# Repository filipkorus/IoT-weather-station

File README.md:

### Development
- [backend README](backend/README.md)
- [frontend README](frontend/README.md)

### Production
Build:
```shell
docker compose -f compose-master.yml -f compose-local.yml build
```

Start:
```shell
docker compose -f compose-master.yml -f compose-local.yml up -d
```

**NOTE:** [example-compose-local.yml](example-compose-local.yml) file is an example how [compose-local.yml](compose-local.yml) file should look like.

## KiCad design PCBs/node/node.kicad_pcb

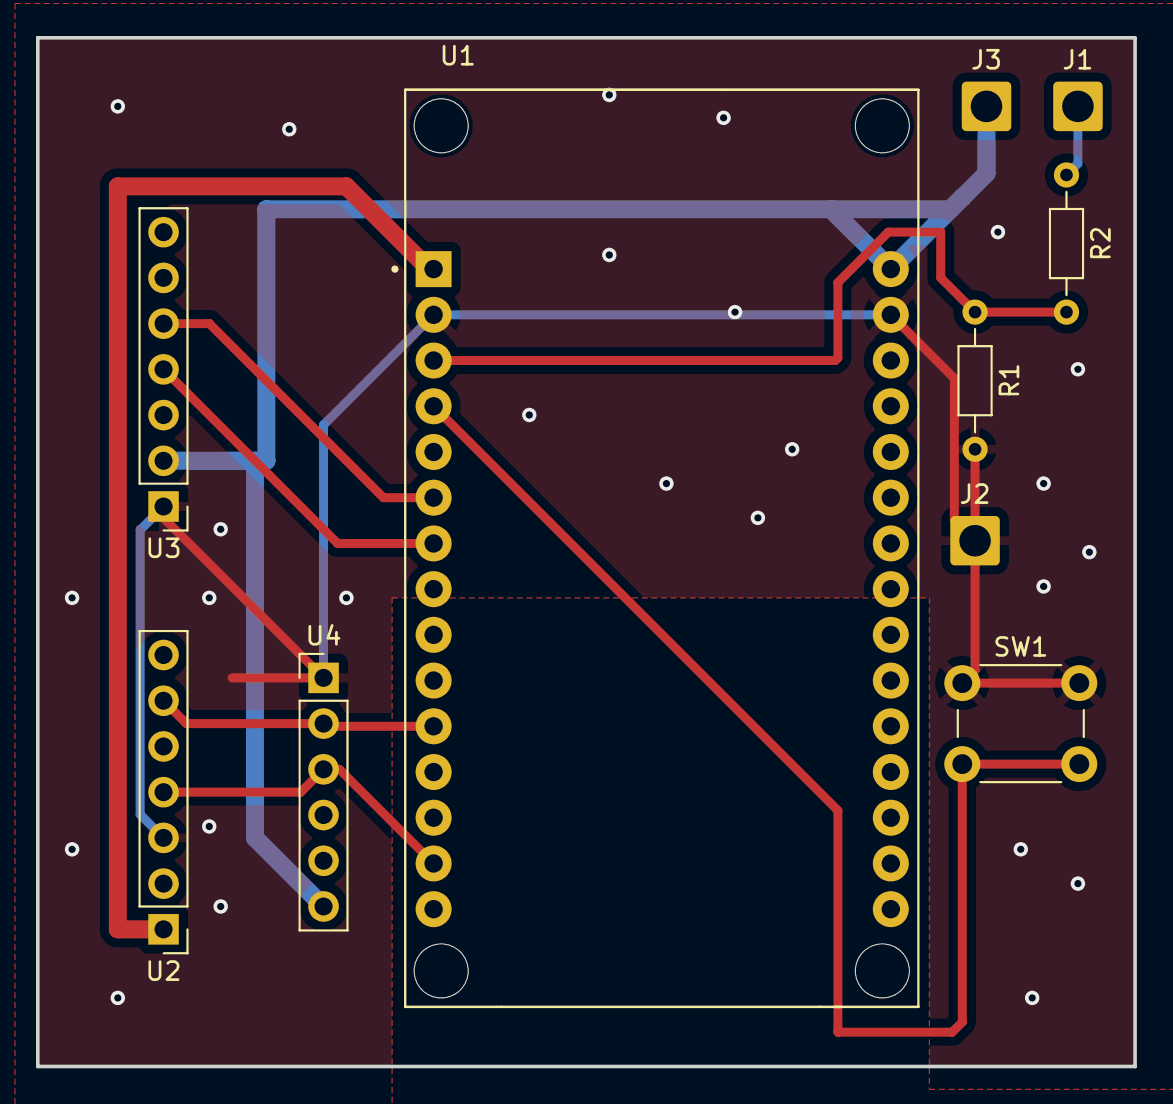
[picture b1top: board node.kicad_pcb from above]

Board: 2 copper layers, 61.0 x 57.2 mm, 10 parts (0 on the bottom side), 10 nets.

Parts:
J1: Bat+; SolderWire-1sqmm_1x01_D1.4mm_OD2.7mm
J2: GND; SolderWire-1sqmm_1x01_D1.4mm_OD2.7mm
J3: 5V; SolderWire-1sqmm_1x01_D1.4mm_OD2.7mm
R1: 10k; R_Axial_DIN0204_L3.6mm_D1.6mm_P7.62mm_Horizontal
R2: 20k; R_Axial_DIN0204_L3.6mm_D1.6mm_P7.62mm_Horizontal
SW1: SW_Push; SW_PUSH_6mm
U1: ESP32-DEVKIT-V1; MODULE_ESP32_DEVKIT_V1
U2: BME280; PinHeader_1x07_P2.54mm_Vertical
U3: pm25sensor; PinHeader_1x07_P2.54mm_Vertical
U4: lidar; PinHeader_1x06_P2.54mm_Vertical

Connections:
+3.3V: U1.1 (3V3), U2.1 (VIN)
+5V: J3.1, U1.30 (VIN), U3.2 (VCC), U4.6 (VCC)
GND: J2.1, R1.2, SW1.1, U1.2 (GND), U1.29 (GND), U2.3 (GND), U3.1 (GND), U4.1 (GND)
unnamed: J1.1, R2.1
unnamed: SW1.2, U1.4 (D2)
unnamed: R1.1, R2.2, U1.3 (D15)
unnamed: U1.11 (D21), U2.6 (SDI), U4.2 (SDA)
unnamed: U1.14 (D22), U2.4 (SCK), U4.3 (SCL)
unnamed: U1.6 (RX2), U3.5 (TX)
unnamed: U1.7 (TX2), U3.4 (RX)

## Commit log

2024-10-13 hotfix
2024-10-13 make WebSockets pass reverse proxy
2024-10-13 page title
2024-10-16 created PIO project with basic test program
2024-10-16 remove .vscode
2024-10-16 Created PIO project with basic test program (#1)
    * created PIO project with basic test program
    * remove .vscode
2024-10-17 broadcast methods implemented
2024-10-17 libs and basic tests
2024-10-17 libs and basic tests (#3)
2024-10-23 added pairing diagram
2024-10-23 more docs
2024-10-23 Added docs for hardware communication (#4)
    * added pairing diagram
    * more docs
2024-10-23 Database schema created, WebSocket authorization added, pairing endpoints done.
2024-10-24 fix and improve 'like' feature
2024-10-24 added Gateway and Node stuff
2024-10-24 Added more communication docs
2024-10-24 Added more communication docs (#6)
2024-10-24 Update Backend Communication Protocol.md (#7)
2024-10-24 docs created, db schema and implementation adjusted
2024-10-31 Created endpoints fetching gateways data.
2024-10-31 add routes
2024-10-31 split routers of public and private gateway endpoints
2024-10-31 typo fix
2024-10-31 Created homepage and subpages which will contain charts, login and register page to go, redirections to subpages done
2024-11-01 Register and Login forms added, Entry page created and started
2024-11-01 minor fixes vol2
2024-11-03 rename gateway endpoint implemented
2024-11-06 dislike functionality added
2024-11-07 [frontend] add prettier
2024-11-07 [frontend] init redux
2024-11-09 improve pairing code validation
2024-11-09 improved account page plus 6digit code button, modified skeleton charts
2024-11-12 auth fix
2024-11-13 chagneing to 2 projects
2024-11-13 chagneing to 2 projects (#21)
2024-11-13 cleanup
2024-11-13 cleanup (#22)
2024-11-13 add sensor data endpoint
2024-11-13 move 'created' property to sensor data
2024-11-13 add measurements endpoints
2024-11-13 weather forecast :)
2024-11-13 fix likes
2024-11-13 sensors and espnow communcation
2024-11-14 extend reverse proxy's connection timeout for WebSocket connections
2024-11-14 kod gateway
2024-11-14 [frontend] remove thing that caused error
2024-11-14 [frontend] connecting frontend-backend 'first' steps
2024-11-14 [frontend] remove console.logs
2024-11-14 [frontend] remove unused import
2024-11-14 [frontend] remove console.log
2024-11-14 [frontend] commented out websocket message logging
2024-11-14 [frontend] remove test component
2024-11-14 [frontend] because [0] is the newest
2024-11-14 [frontend] fix receiving live gateway data
2024-11-14 [frontend] remove debug elements
2024-11-14 [frontend] fix socket connection
2024-11-14 [frontend] sending likes works
2024-11-14 [frontend] websocket part nearly finished
2024-11-14 [frontend] add sendMessage to useSocket
2024-11-14 [frontend] prod urls
2024-11-14 [frontend] sending like works
2024-11-14 add latitude and longitude to the gw
2024-11-14 minor fix
2024-11-14 sensors and espnow communcation (#25)
2024-11-14 kod gateway (#28)
2024-11-14 add ping-pong events to check if gateway is still connected
2024-11-14 working node sensors with espnow
2024-11-14 working node sensors with espnow (#29)
2024-11-14 pcb noe
2024-11-14 @matij/pcb (#30)
    * pcb noe
    * changes
2024-11-15 remove 'version' from docker compose
2024-11-15 minor fixes
2024-11-16 account page imporved, bar charts, responsive grid
2024-11-17 added STL files
2024-11-17 @matij/case stl (#33)
    * pcb noe
    * changes
    * added STL files
2024-11-20 schem gateway
2024-11-20 @matij/schem gateway (#34)
    * schem gateway
    * changes
2024-11-20 dziala
2024-11-20 Integration hardware (#35)
2024-11-20 better case
2024-11-20 better case (#36)
2024-11-20 nie chce mi sie robic prow
2024-11-20 nie chce mi sie robic prow (#37)
2024-11-20 wdadwdwadaw
2024-11-20 wdadwdwadaw (#38)
2024-11-21 lajki sie nie blokują, a dane pobierają na początku
2024-11-21 pobieranie lokalizacji do pogody
2024-11-21 add register logic
2024-11-21 fix data presentation and prettify code
2024-11-21 0 is also falsy ;)
2024-11-21 do not round PMx
2024-11-21 fix saving node data
2024-11-21 add websocket debugging logs
2024-11-21 make builds faster
2024-11-25 add measurements docs and fix typo
2024-11-26 [frontend] fix live sensor data parsing
2024-11-26 [frontend] login, logout & bearer including logic
2024-11-26 [frontend] login, logout, and pairing
2024-11-26 [frontend] display stations owned by the current user in their private panel
2024-11-26 [frontend] reload private stations after pairing
2024-11-26 fix likes?
2024-11-27 add likes event
2024-11-27 hardware skonczony
2024-11-27 @matij/dobra robie tu do konca (#47)
    * dwd
    * hardware skonczony
    * hardware skonczony
    * cli
2024-11-27 vendor REST API created
2024-11-27 minor changes + added removing the station and changing name of the station
2024-11-27 replaced removing station with localization
2024-11-27 console log '.' when refresh failure
2024-11-27 error and redirect when non-existing slope
2024-11-27 don't refresh gateways after successful pairing
2024-11-27 wyswietl jaki blad przy rejestracji z error mesasge
2024-11-27 show 'brak stacji' if brak stacji
2024-11-27 display station name correctly once more
2024-11-27 remove access token on logout
2024-11-27 fix types
2024-11-27 redirect to /login from /account if not logged in
2024-11-27 redirect to /login from /account if not logged in (#52)
2024-11-27 automatic redirect to /account form /login and from /register if logged in
2024-11-27 automatic redirect to /account form /login and from /register if logged in (#54)
2024-11-27 updating gateway coordinates
2024-11-27 gateway location updating, redirect to /account if logged in
    * automatic redirect to /account form /login and from /register if logged in
    * updating gateway coordinates
    ---------
2024-11-27 improved localization and renaming
2024-11-27 improved localization and renaming (#56)
    * improved localization and renaming
    * Merge branch 'main' into @ola/ui
    ---------
2024-11-27 remove unused console.log
    remove unused console.log
    ---------
2024-11-27 [frontend] edit station name
2024-11-27 [frontend] edit station name
    [frontend] edit station name
    ---------
2024-11-27 hardware skonczony (#59)
    * dwd
    * hardware skonczony
    * hardware skonczony
    * cli
    * xD
2024-11-27 better docs
2024-11-27 better docs (#60)
2024-11-27 [frontend] fix frontend logic when pairing
2024-11-27 [frontend] fix frontend logic when pairing
    * [frontend] fix frontend logic when pairing
    ---------
2024-11-27 ola zrobila wykresy
2024-11-27 [frontend] likes first time error display
2024-11-27 [frontend] pairing stations fix, likes first time error display thingy
    * automatic redirect to /account form /login and from /register if logged in
    * updating gateway coordinates
    * [frontend] edit station name
    * [frontend] fix frontend logic when pairing
    * [frontend] likes first time error display
    ---------
2024-11-27 kind of still works
2024-11-27 final fixes
2024-11-28 [frontend] displaying archival data
2024-11-28 @mp/koniec (#64)
    * kind of still works
    * [frontend] displaying archival data
    ---------
2024-11-28 [frontend] fix build not building
2024-11-28 @mp/koniec (#65)
    * kind of still works
    * .
    * [frontend] displaying archival data
    * [frontend] fix build not building
    ---------
2024-11-28 [frontend] prevent locking user when their token expires and they don't want to sign in
2024-11-28 @mp/koniec (#66)
    * kind of still works
    * .
    * [frontend] displaying archival data
    * [frontend] fix build not building
    * [frontend] prevent locking user when their token expires and they don't want to sign in
    ---------
2024-11-28 @mp/koniec (#67)
    * kind of still works
    * .
    * [frontend] displaying archival data
    * [frontend] fix build not building
    * [frontend] prevent locking user when their token expires and they don't want to sign in
    * [frontend] fix build not building
2024-11-28 add account btn
2024-11-28 final improvements
2024-11-28 quick fix
2024-11-28 chart fix
2024-11-28 added month name
2024-11-28 manual flow in CLI (#69)
2024-12-01 poprawki
2024-12-04 Created PIO project with basic test program
    * created PIO project with basic test program
    * remove .vscode
2024-12-04 display battery level
2024-12-04 fix backend/Dockerfile
2024-12-04 fix 24h chart
2024-12-04 add snackbar with battery level
2024-12-04 poprawki (#70)
2024-12-04 fix after rebase
2024-12-05 architecture
